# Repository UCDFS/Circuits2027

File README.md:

# UCDFS Circuits Repository 2027

Welcome to the University College Dublin Formula Student (UCDFS) KiCad circuits repository! This is the central location for all our electronic circuit designs, schematics, and PCB layouts.
This is a fresh repo for the 2027 competition.

## About

This repository contains KiCad project files for various electronic circuits used in our Formula Student vehicle and projects. All designs are created using KiCad, an open-source electronic design automation (EDA) suite.

## Getting Started

1. **Clone this repository:**
   ```bash
   git clone https://github.com/UCDFS/Circuits.git
   cd Circuits
   ```

2. **Open a project in KiCad:**
   - Launch KiCad
   - Open the `.kicad_pro` file for the project you want to work on
   - The schematic (`.kicad_sch`) and PCB layout (`.kicad_pcb`) will be accessible from the project manager

3. **View/Edit Schematics:**
   - Click "Schematic Editor" in KiCad's main window
   - Or directly open the `.kicad_sch` file

4. **View/Edit PCB Layout:**
   - Click "PCB Editor" in KiCad's main window
   - Or directly open the `.kicad_pcb` file

## Repository Structure

```
├── README.md                     # This file
├── .gitignore                    # Git ignore rules for KiCad projects
└── [Project Name]/               # Individual circuit projects
    ├── [Project].kicad_pro       # KiCad project file
    ├── [Project].kicad_sch       # Schematic file
    └── [Project].kicad_pcb       # PCB layout file
```

## Contributing

When contributing new circuits or modifications:

1. **Create a new branch** for your work
2. **Organize projects** in clearly named directories
3. **Follow naming conventions:** Use descriptive names for projects and files
4. **Include all necessary files:** Ensure `.kicad_pro`, `.kicad_sch`, and `.kicad_pcb` files are included
5. **Document your work:** Add project details to a README in each circuit subfolder

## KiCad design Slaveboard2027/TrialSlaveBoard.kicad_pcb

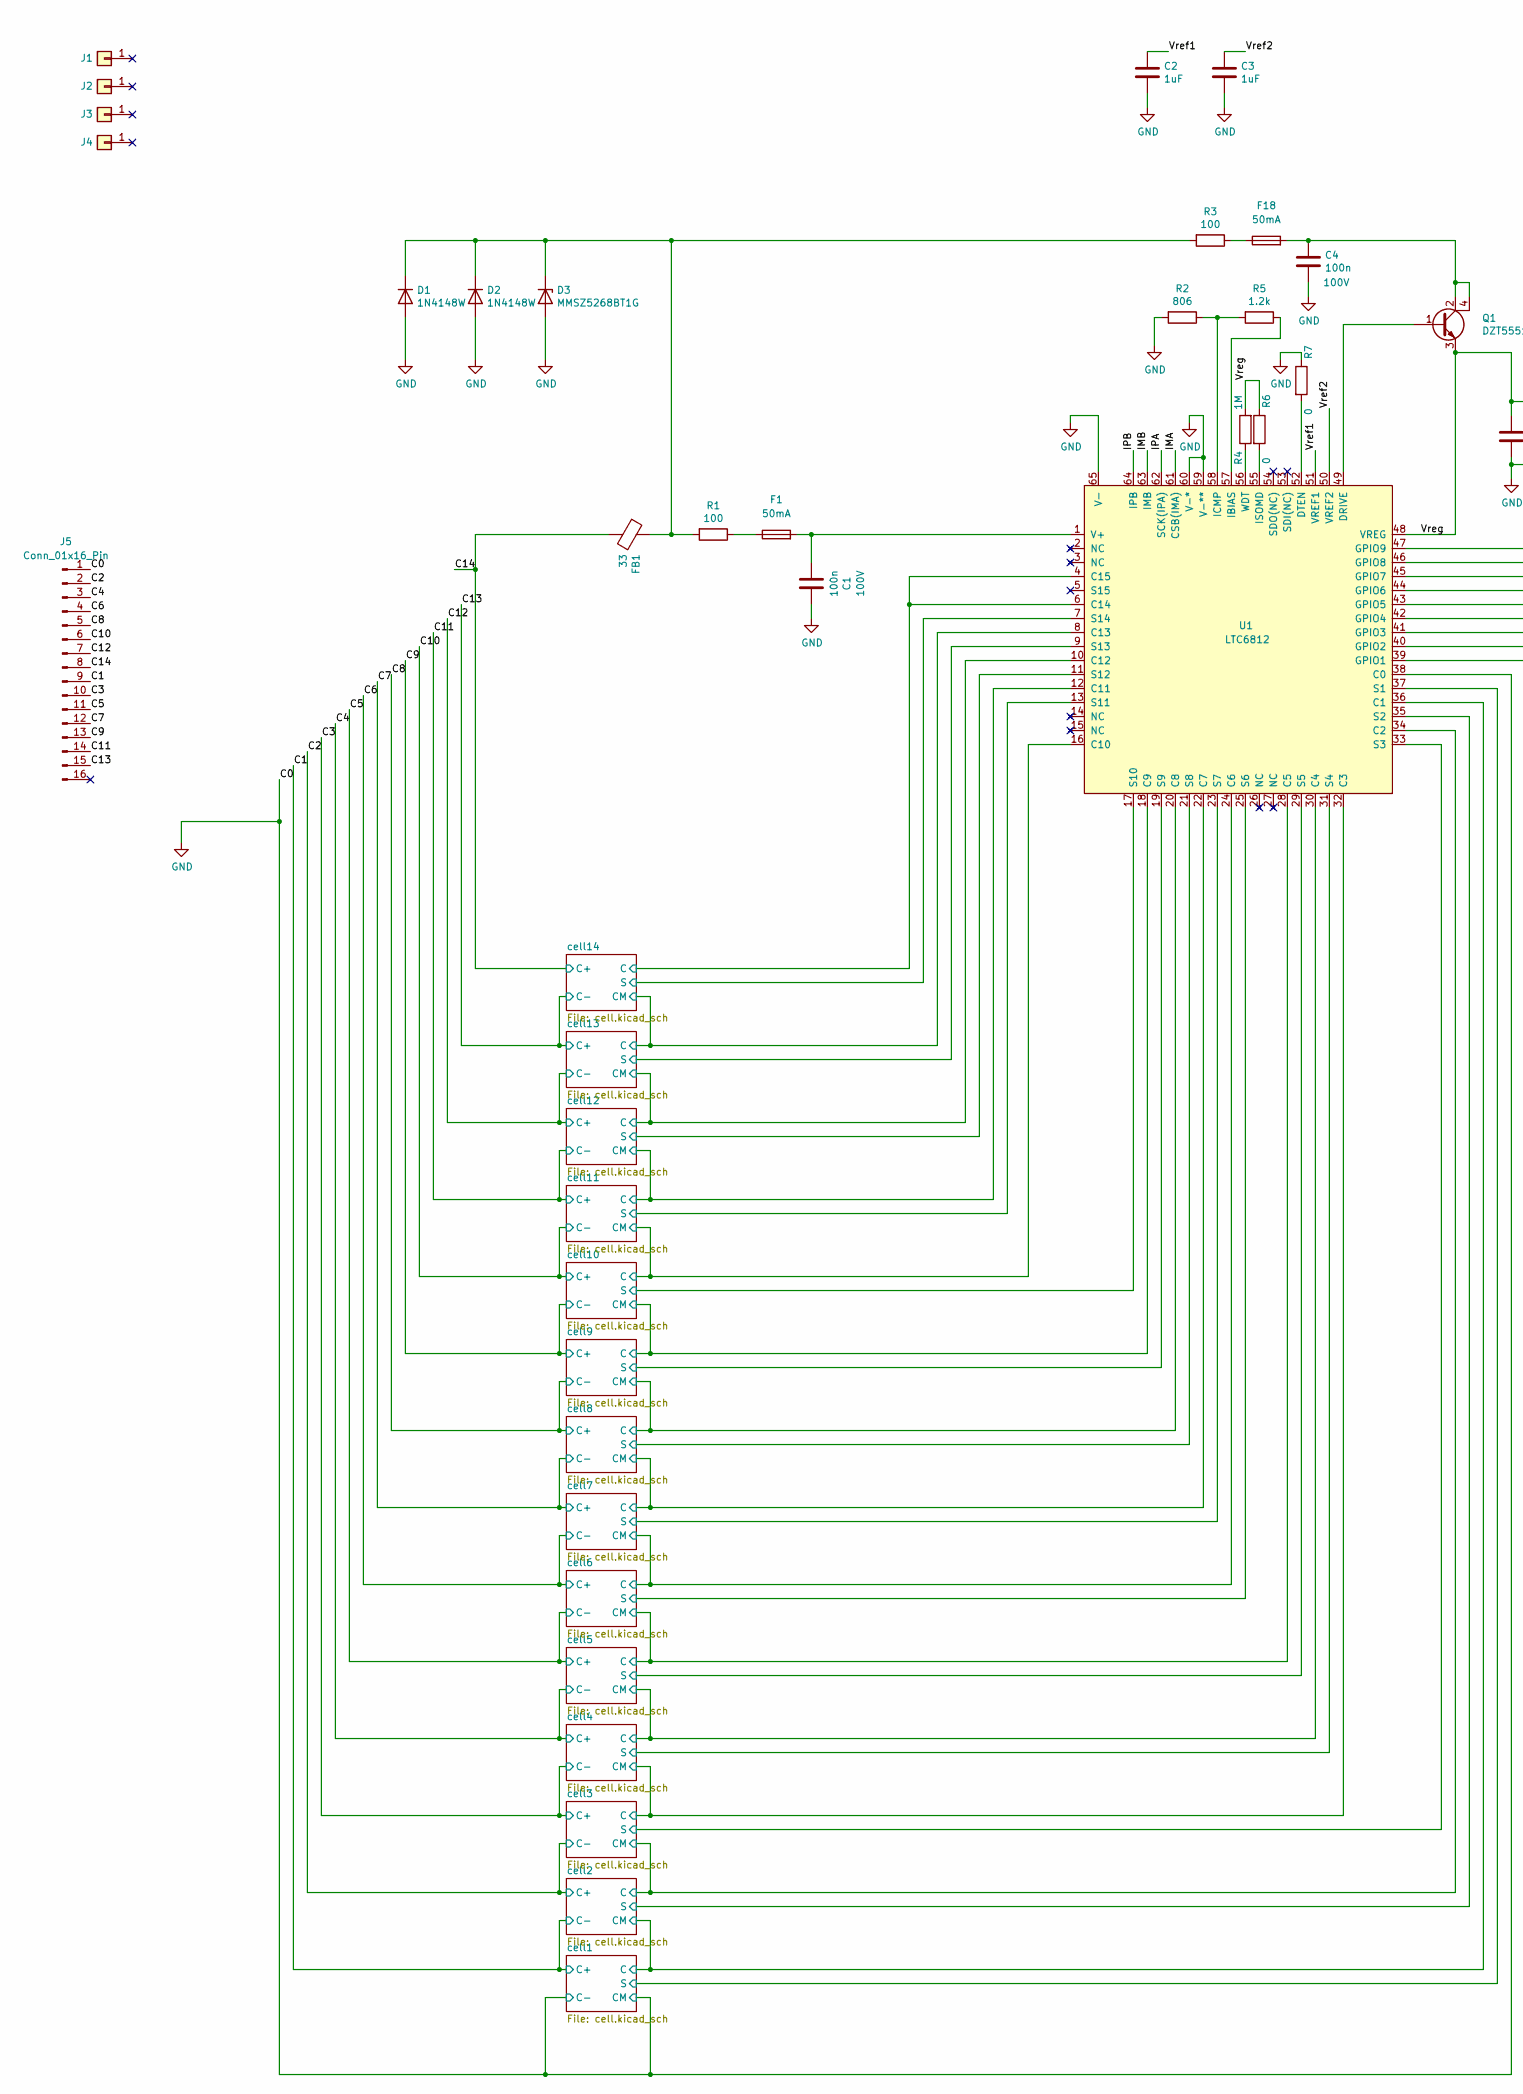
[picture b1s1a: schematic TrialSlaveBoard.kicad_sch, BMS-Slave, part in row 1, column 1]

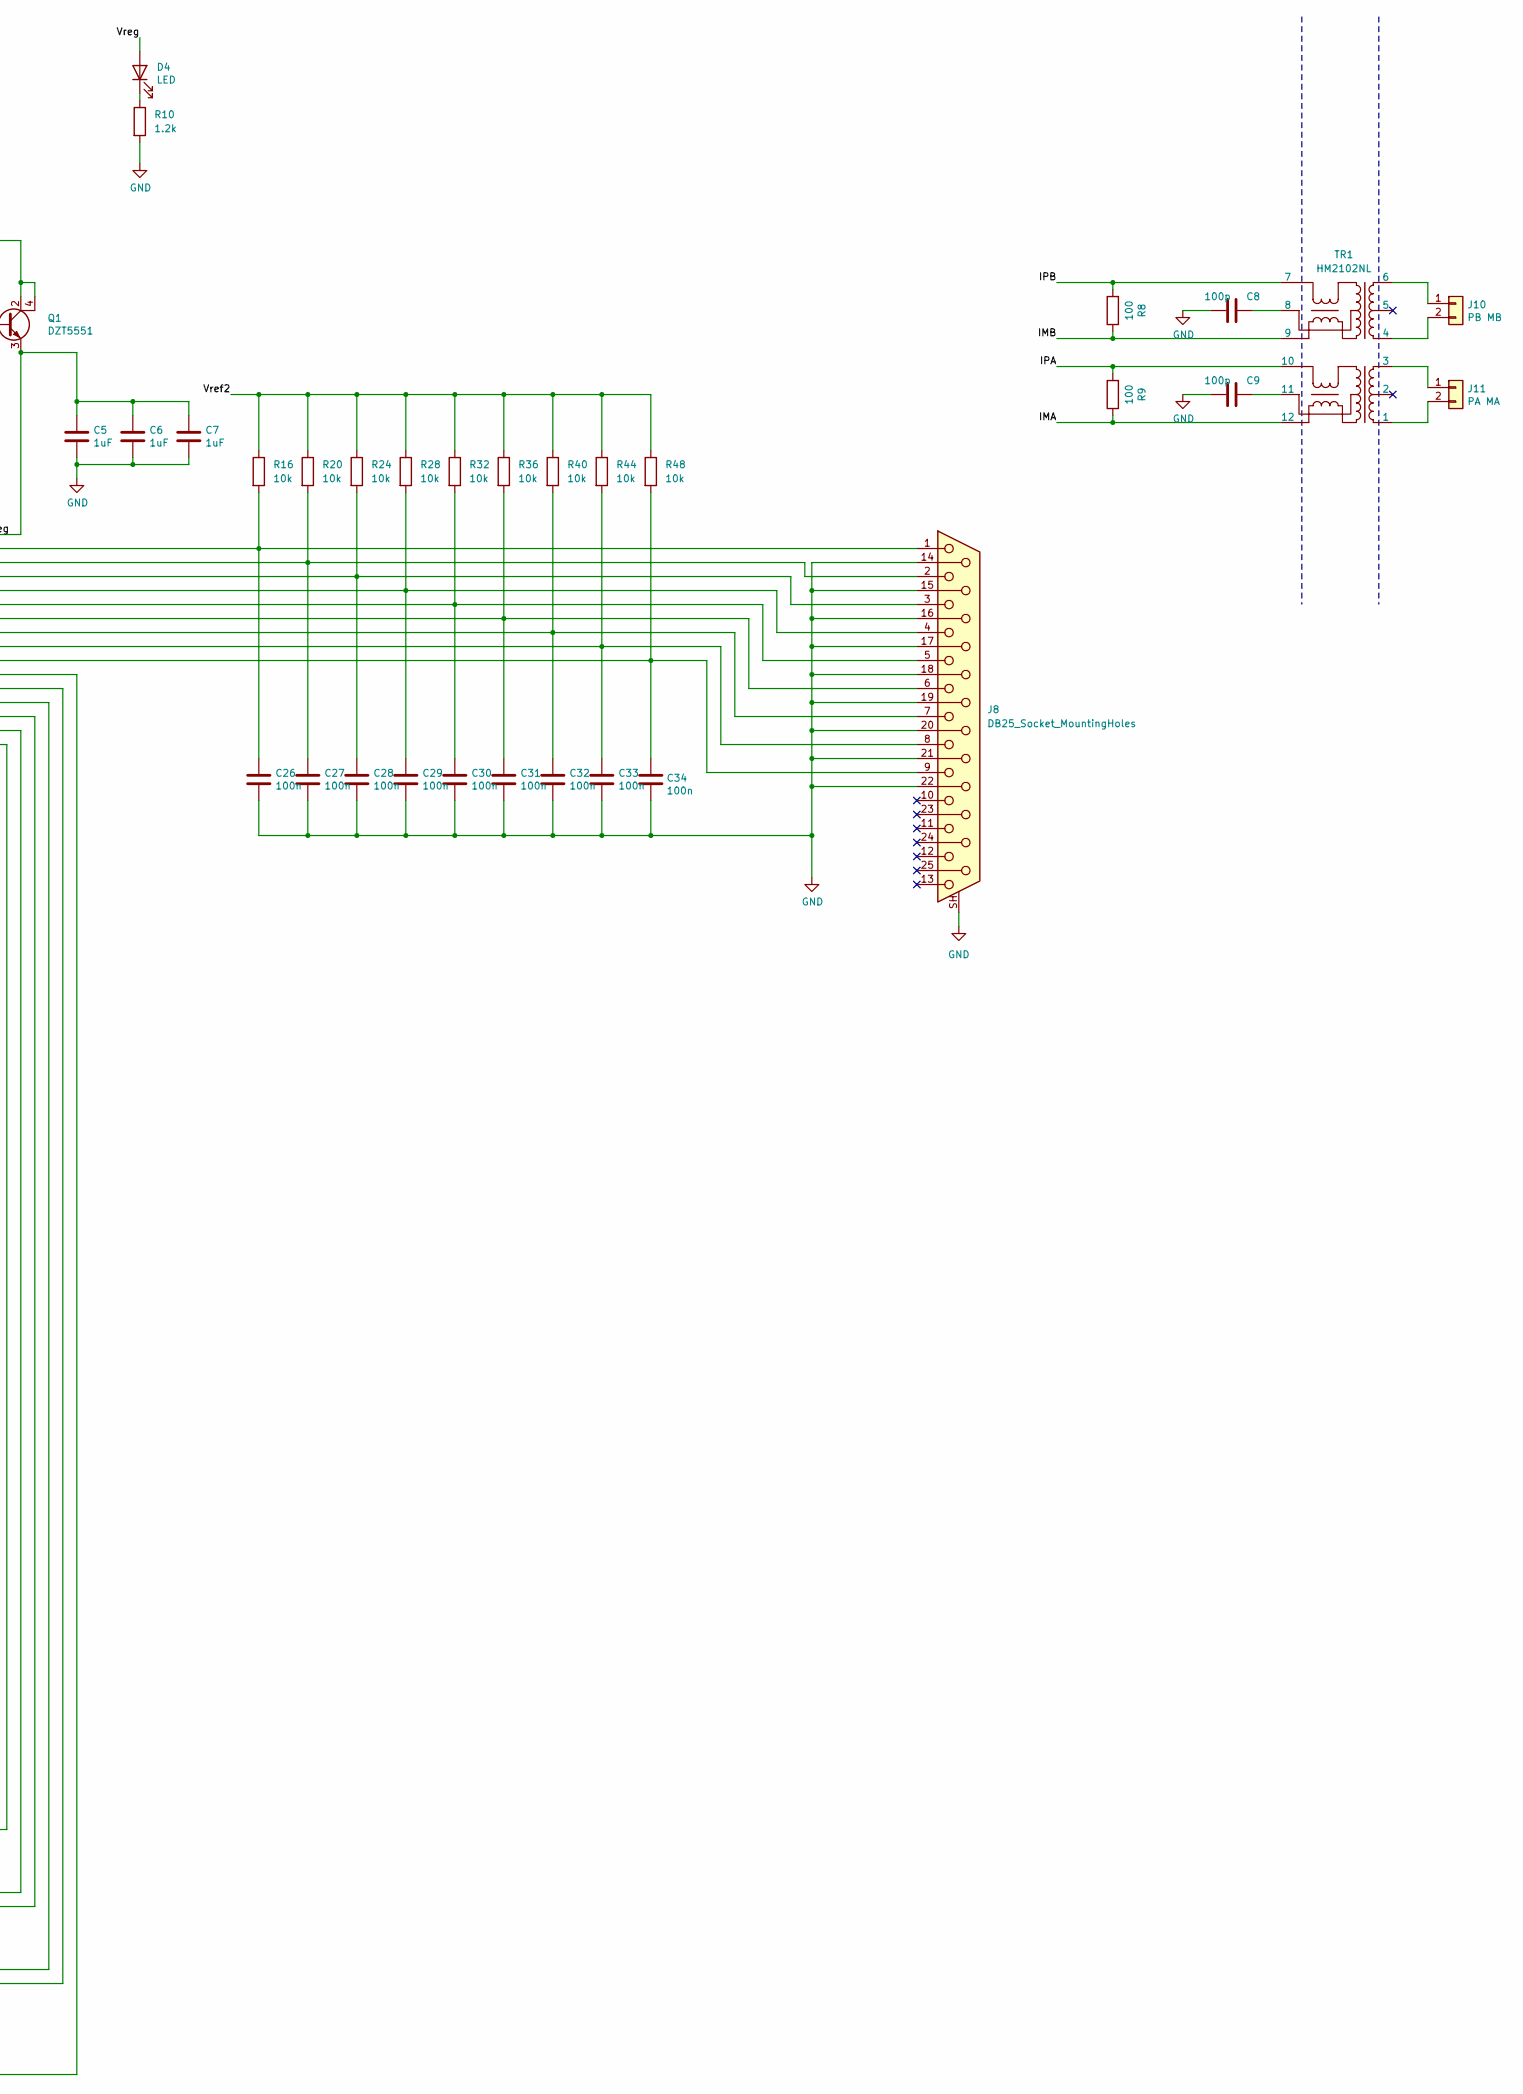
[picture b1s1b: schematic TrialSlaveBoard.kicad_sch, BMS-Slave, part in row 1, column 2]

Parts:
C1, C4: 100n; C_0603_1608Metric; Voltage 100V; MPN GRM188R72A104KA35D
C2, C3, C5, C6, C7: 1uF; C_0603_1608Metric; MPN CL10B105KP8NNNC
C8, C9: 100p; C_0603_1608Metric; MPN GRM1885C1H101JA01D
C26, C27, C28, C29, C30, C31, C32, C33, C34: 100n; C_0603_1608Metric; MPN GRM188R72A104KA35D
D1, D2: 1N4148W; D_SOD-123; MPN 1N4148W-7-F
D3: MMSZ5268BT1G; D_SOD-123; MPN MMSZ5268BT1G
D4: LED; LED_0603_1608Metric_Pad1.05x0.95mm_HandSolder
F1, F18: 50mA; Fuse_1206_3216Metric; Part Number 3413.0002.11
FB1: 33; R_0603_1608Metric; MPN BLM18PG330SN1D
J1, J2, J3, J4: Conn_01x01; MountingHole_3.2mm_M3_ISO7380_Pad
J5: Conn_01x16_Pin; Molex_Micro-Fit_3.0_43045-1600_2x08_P3.00mm_Horizontal
J8: DB25_Socket_MountingHoles; DSUB-25_Female_Horizontal_P2.77x2.54mm_EdgePinOffset10.40mm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
J10: PB MB; Molex_Micro-Fit_3.0_43650-0200_1x02_P3.00mm_Horizontal; Part No. 43650-0202
J11: PA MA; Molex_Micro-Fit_3.0_43650-0200_1x02_P3.00mm_Horizontal; Part No. 43650-0202
Q1: DZT5551; SOT-223; MPN DZT5551-13
R1, R3: 100; R_0805_2012Metric; MPN CRCW0805100RFKEAHP
R2: 806; R_0603_1608Metric
R4: 1M; R_0603_1608Metric
R5, R10: 1.2k; R_0603_1608Metric
R6, R7: 0; R_0603_1608Metric
R8, R9: 100; R_0805_2012Metric
R16, R20, R24, R28, R32, R36, R40, R44, R48: 10k; R_0603_1608Metric
TR1: HM2102NL
U1: LTC6812; TQFP-64-1EP_10x10mm_P0.5mm_EP8x8mm

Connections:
/C1: J5.9; also elsewhere on the board
/C2: J5.2; also elsewhere on the board
/C3: J5.10; also elsewhere on the board
/C4: J5.3; also elsewhere on the board
/C5: J5.11; also elsewhere on the board
/C6: J5.4; also elsewhere on the board
/C7: J5.12; also elsewhere on the board
/C8: J5.5; also elsewhere on the board
/C9: J5.13; also elsewhere on the board
/C10: J5.6; also elsewhere on the board
/C11: J5.14; also elsewhere on the board
/C12: J5.7; also elsewhere on the board
/C13: J5.15; also elsewhere on the board
/C14: FB1.2, J5.8; also elsewhere on the board
/IMA: R9.1, TR1.12, U1.61 (CSB(IMA))
/IMB: R8.1, TR1.9, U1.63 (IMB)
/IPA: R9.2, TR1.10, U1.62 (SCK(IPA))
/IPB: R8.2, TR1.7, U1.64 (IPB)
/Vref1: C2.2, U1.51 (VREF1)
/Vref2: C3.2, R16.1, R20.1, R24.1, R28.1, R32.1, R36.1, R40.1, R44.1, R48.1, U1.50 (VREF2)
/Vreg: C5.2, C6.2, C7.2, D4.2 (A), Q1.3 (E), R4.2, R6.1, U1.48 (VREG)
/cell1/C: U1.36 (C1); also elsewhere on the board
/cell1/S: U1.37 (S1); also elsewhere on the board
/cell2/C: U1.34 (C2); also elsewhere on the board
/cell2/S: U1.35 (S2); also elsewhere on the board
/cell3/C: U1.32 (C3); also elsewhere on the board
/cell3/S: U1.33 (S3); also elsewhere on the board
/cell4/C: U1.30 (C4); also elsewhere on the board
/cell4/S: U1.31 (S4); also elsewhere on the board
/cell5/C: U1.28 (C5); also elsewhere on the board
/cell5/S: U1.29 (S5); also elsewhere on the board
/cell6/C: U1.24 (C6); also elsewhere on the board
/cell6/S: U1.25 (S6); also elsewhere on the board
/cell7/C: U1.22 (C7); also elsewhere on the board
/cell7/S: U1.23 (S7); also elsewhere on the board
/cell8/C: U1.20 (C8); also elsewhere on the board
/cell8/S: U1.21 (S8); also elsewhere on the board
/cell9/S: U1.19 (S9); also elsewhere on the board
/cell10/C: U1.16 (C10); also elsewhere on the board
/cell10/CM: U1.18 (C9); also elsewhere on the board
/cell10/S: U1.17 (S10); also elsewhere on the board
/cell11/C: U1.12 (C11); also elsewhere on the board
/cell11/S: U1.13 (S11); also elsewhere on the board
/cell12/C: U1.10 (C12); also elsewhere on the board
/cell12/S: U1.11 (S12); also elsewhere on the board
/cell13/C: U1.8 (C13); also elsewhere on the board
/cell13/S: U1.9 (S13); also elsewhere on the board
/cell14/C: U1.4 (C15), U1.6 (C14); also elsewhere on the board
/cell14/S: U1.7 (S14); also elsewhere on the board
GND: C1.1, C2.1, C3.1, C4.1, C5.1, C6.1, C7.1, C8.1, C9.1, C26.2, C27.2, C28.2, C29.2, C30.2, C31.2, C32.2, C33.2, C34.2, D1.2 (A), D2.2 (A), D3.2 (A), J5.1, J8.14, J8.15, J8.16, J8.17, J8.18, J8.19, J8.20, J8.21, J8.22, J8.SH (PAD), R2.2, R7.1, R10.2, U1.38 (C0), U1.59 (V-**), U1.60 (V-*), U1.65 (V-); also elsewhere on the board
unnamed: C4.2, F18.2, Q1.2 (C), Q1.4 (C)
unnamed: C8.2, TR1.8
unnamed: C9.2, TR1.11
unnamed: D1.1 (K), D2.1 (K), D3.1 (K), FB1.1, R1.2, R3.2
unnamed: D4.1 (K), R10.1
unnamed: F1.1, R1.1
unnamed: F18.1, R3.1
unnamed: J10.1, TR1.6
unnamed: J10.2, TR1.4
unnamed: J11.1, TR1.3
unnamed: J11.2, TR1.1
unnamed: Q1.1 (B), U1.49 (DRIVE)
unnamed: R7.2, U1.52 (DTEN)
unnamed: C34.1, J8.9, R48.2, U1.39 (GPIO1)
unnamed: C33.1, J8.8, R44.2, U1.40 (GPIO2)
unnamed: C32.1, J8.7, R40.2, U1.41 (GPIO3)
unnamed: C31.1, J8.6, R36.2, U1.42 (GPIO4)
unnamed: C30.1, J8.5, R32.2, U1.43 (GPIO5)
unnamed: C29.1, J8.4, R28.2, U1.44 (GPIO6)
unnamed: C28.1, J8.3, R24.2, U1.45 (GPIO7)
unnamed: C27.1, J8.2, R20.2, U1.46 (GPIO8)
unnamed: C26.1, J8.1, R16.2, U1.47 (GPIO9)
unnamed: R5.1, U1.57 (IBIAS)
unnamed: R2.1, R5.2, U1.58 (ICMP)
unnamed: R6.2, U1.55 (ISOMD)
unnamed: C1.2, F1.2, U1.1 (V+)
unnamed: R4.1, U1.56 (WDT)

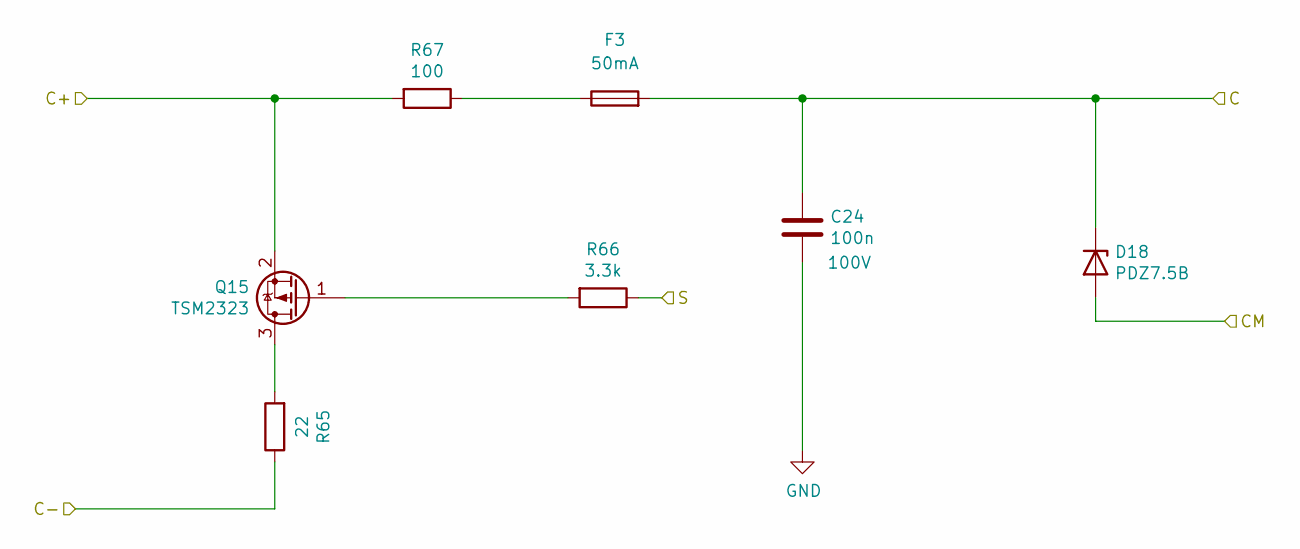
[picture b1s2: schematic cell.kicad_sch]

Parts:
C24: 100n; C_0603_1608Metric; Voltage 100V; MPN GRM188R72A104KA35D
D18: PDZ7.5B; D_SOD-323; MPN PDZ7.5B
F3: 50mA; Fuse_1206_3216Metric; Part Number 3413.0002.11
Q15: TSM2323; SOT-23
R65: 22; R_2512_6332Metric; MPN YAGEO AC2512JK-7W22RL
R66: 3.3k; R_0508_1220Metric; MPN KOA WK73R2ATTD3301F
R67: 100; R_0805_2012Metric_Pad1.20x1.40mm_HandSolder; MPN Vishay CRCW0805100RFKEAHP

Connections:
/C13: R65.1; also elsewhere on the board
/C14: Q15.2 (S), R67.2; also elsewhere on the board
/cell13/C: D18.2 (A); also elsewhere on the board
/cell14/C: C24.2, D18.1 (K), F3.2; also elsewhere on the board
/cell14/S: R66.1; also elsewhere on the board
GND: C24.1; also elsewhere on the board
unnamed: F3.1, R67.1
unnamed: Q15.3 (D), R65.2
unnamed: Q15.1 (G), R66.2

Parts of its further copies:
C11, C12, C13, C14, C15, C16, C17, C18, C19, C20, C21, C22, C23: 100n; C_0603_1608Metric; Voltage 100V; MPN GRM188R72A104KA35D
D5, D6, D7, D8, D9, D10, D11, D12, D13, D14, D15, D16, D17: PDZ7.5B; D_SOD-323; MPN PDZ7.5B
F4, F5, F6, F7, F8, F9, F10, F11, F12, F13, F14, F15, F16: 50mA; Fuse_1206_3216Metric; Part Number 3413.0002.11
Q2, Q3, Q4, Q5, Q6, Q7, Q8, Q9, Q10, Q11, Q12, Q13, Q14: TSM2323; SOT-23
R13, R17, R21, R25, R29, R33, R37, R41, R45, R49, R53, R57, R61: 22; R_2512_6332Metric; MPN YAGEO AC2512JK-7W22RL
R14, R18, R22, R26, R30, R34, R38, R42, R46, R50, R54, R58, R62: 3.3k; R_0508_1220Metric; MPN KOA WK73R2ATTD3301F
R15, R19, R23, R27, R31, R35, R39, R43, R47, R51, R55, R59, R63: 100; R_0805_2012Metric_Pad1.20x1.40mm_HandSolder; MPN Vishay CRCW0805100RFKEAHP

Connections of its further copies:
/C1: Q2.2 (S), R15.2, R17.1; also elsewhere on the board
/C2: Q3.2 (S), R19.2, R21.1; also elsewhere on the board
/C3: Q4.2 (S), R23.2, R25.1; also elsewhere on the board
/C4: Q5.2 (S), R27.2, R29.1; also elsewhere on the board
/C5: Q6.2 (S), R31.2, R33.1; also elsewhere on the board
/C6: Q7.2 (S), R35.2, R37.1; also elsewhere on the board
/C7: Q8.2 (S), R39.2, R41.1; also elsewhere on the board
/C8: Q9.2 (S), R43.2, R45.1; also elsewhere on the board
/C9: Q10.2 (S), R47.2, R49.1; also elsewhere on the board
/C10: Q11.2 (S), R51.2, R53.1; also elsewhere on the board
/C11: Q12.2 (S), R55.2, R57.1; also elsewhere on the board
/C12: Q13.2 (S), R59.2, R61.1; also elsewhere on the board
/C13: Q14.2 (S), R63.2; also elsewhere on the board
/cell1/C: C11.2, D5.1 (K), D6.2 (A), F16.2; also elsewhere on the board
/cell1/S: R14.1; also elsewhere on the board
/cell2/C: C12.2, D6.1 (K), D7.2 (A), F15.2; also elsewhere on the board
/cell2/S: R18.1; also elsewhere on the board
/cell3/C: C13.2, D7.1 (K), D8.2 (A), F14.2; also elsewhere on the board
/cell3/S: R22.1; also elsewhere on the board
/cell4/C: C14.2, D8.1 (K), D9.2 (A), F13.2; also elsewhere on the board
/cell4/S: R26.1; also elsewhere on the board
/cell5/C: C15.2, D9.1 (K), D10.2 (A), F12.2; also elsewhere on the board
/cell5/S: R30.1; also elsewhere on the board
/cell6/C: C16.2, D10.1 (K), D11.2 (A), F11.2; also elsewhere on the board
/cell6/S: R34.1; also elsewhere on the board
/cell7/C: C17.2, D11.1 (K), D12.2 (A), F10.2; also elsewhere on the board
/cell7/S: R38.1; also elsewhere on the board
/cell8/C: C18.2, D12.1 (K), D13.2 (A), F9.2; also elsewhere on the board
/cell8/S: R42.1; also elsewhere on the board
/cell9/S: R46.1; also elsewhere on the board
/cell10/C: C20.2, D14.1 (K), D15.2 (A), F7.2; also elsewhere on the board
/cell10/CM: C19.2, D13.1 (K), D14.2 (A), F8.2; also elsewhere on the board
/cell10/S: R50.1; also elsewhere on the board
/cell11/C: C21.2, D15.1 (K), D16.2 (A), F6.2; also elsewhere on the board
/cell11/S: R54.1; also elsewhere on the board
/cell12/C: C22.2, D16.1 (K), D17.2 (A), F5.2; also elsewhere on the board
/cell12/S: R58.1; also elsewhere on the board
/cell13/C: C23.2, D17.1 (K), F4.2; also elsewhere on the board
/cell13/S: R62.1; also elsewhere on the board
GND: C11.1, C12.1, C13.1, C14.1, C15.1, C16.1, C17.1, C18.1, C19.1, C20.1, C21.1, C22.1, C23.1, D5.2 (A), R13.1; also elsewhere on the board
unnamed: F4.1, R63.1
unnamed: F5.1, R59.1
unnamed: F6.1, R55.1
unnamed: F7.1, R51.1
unnamed: F8.1, R47.1
unnamed: F9.1, R43.1
unnamed: F10.1, R39.1
unnamed: F11.1, R35.1
unnamed: F12.1, R31.1
unnamed: F13.1, R27.1
unnamed: F14.1, R23.1
unnamed: F15.1, R19.1
unnamed: F16.1, R15.1
unnamed: Q2.3 (D), R13.2
unnamed: Q2.1 (G), R14.2
unnamed: Q3.3 (D), R17.2
unnamed: Q3.1 (G), R18.2
unnamed: Q4.3 (D), R21.2
unnamed: Q4.1 (G), R22.2
unnamed: Q5.3 (D), R25.2
unnamed: Q5.1 (G), R26.2
unnamed: Q6.3 (D), R29.2
unnamed: Q6.1 (G), R30.2
unnamed: Q7.3 (D), R33.2
unnamed: Q7.1 (G), R34.2
unnamed: Q8.3 (D), R37.2
unnamed: Q8.1 (G), R38.2
unnamed: Q9.3 (D), R41.2
unnamed: Q9.1 (G), R42.2
unnamed: Q10.3 (D), R45.2
unnamed: Q10.1 (G), R46.2
unnamed: Q11.3 (D), R49.2
unnamed: Q11.1 (G), R50.2
unnamed: Q12.3 (D), R53.2
unnamed: Q12.1 (G), R54.2
unnamed: Q13.3 (D), R57.2
unnamed: Q13.1 (G), R58.2
unnamed: Q14.3 (D), R61.2
unnamed: Q14.1 (G), R62.2

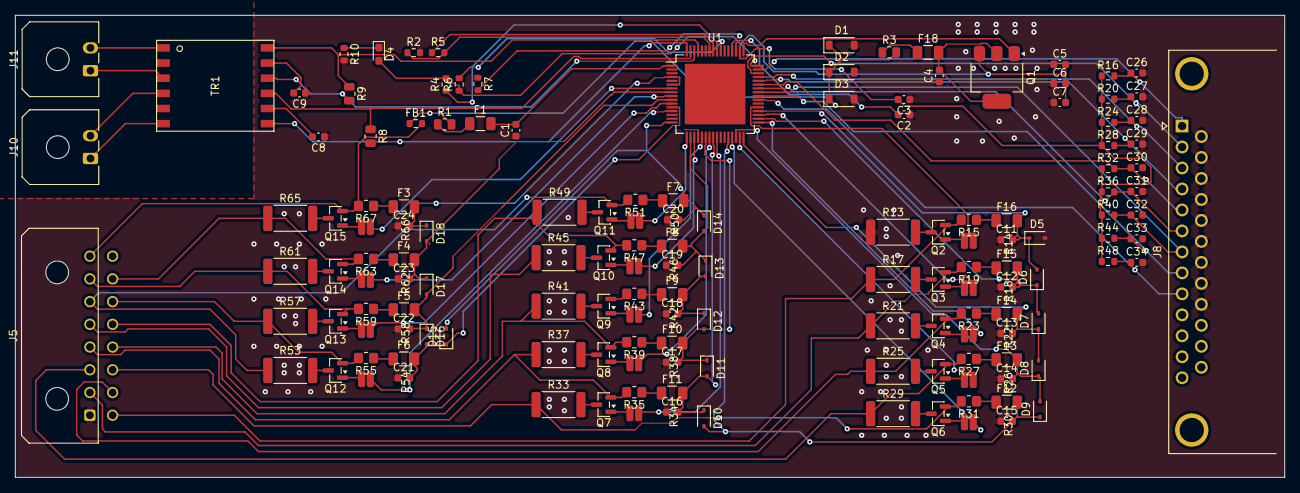
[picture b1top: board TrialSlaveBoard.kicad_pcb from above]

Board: 2 copper layers, 167.6 x 61.0 mm, 149 parts (0 on the bottom side), 119 nets.
